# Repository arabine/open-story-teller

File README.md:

# Open Story Teller (OST)

|  Job | Status  |
|---|---|
| Story Editor  |   |

Open Story Teller is an Open Source project to provide guidelines and software to build your own story teller box (electronics, mechanical).

The main goal is to *not* make electronics boards but instead buy or reuse existing ones. This will allow you to easily repair your device with spare parts.

We propose a set of parts and firmware that is working well together but your are free to custom everything to fit your needs.

This project can be used as a base platform for any device that is composed by:
- A display (TFT...)
- An Audio output
- A SD card or memory
- Some Buttons / rotary encoder / potentiometer

<hr >

# Links

- http://openstoryteller.org/: main documentation, project news, guidelines, hardware shoping list...
- http://github.com/arabine/open-story-teller: source code, tickets, help

# Hardware parts

We propose the concept of bundles: a set of electronic boards that you can purchase quite easily (eg: Arduino, SeedStudio, Pimoroni, Adafruit, SparkFun...). The bundles are built around a central main board, the CPU, which comes with more or less peripherals (SD-Card reader, Wifi...).

Several bundles will be officially supported ; this is needed for us to ensure the portability of the firmware hardware interface layer.

Current bundles:
- Raspberry Pico (official DevKit) (ARM Cortex M0+)
- RISC-V based board (GD32VF103)

We plan to propose a mechanical enclosure ready to be printed for an official bundle.

See the documentation!

# Generic player architecture

The base software is highly portable and includes a micro virtual machine that executes the story scenario. This allow potential complex stories with loops, branches, user choices, randomization...

This project propose an minimal cross-platform GUI player application that can be used as a base project and VM implementation reference.

# StoryTeller Editor

We propose a basic editor tool to create your own stories. The generated story script runs on our micro virtual machine and allow generate complex stories.

Work in progress:
- Project management
- Story pack generation
- Basic nodes (media nodes, start and stop)

Planned nodes:
- Random
- Loop
- Conditional

# Story Player

The Story plater is a purely software implementation of a simple story player. It is provided as an example and a test device for the micro virtual machine. It is very portable and should run on a large number of platforms.

There are multiple implementations in this directory (Flutter, SDL, Raylib). The one that will be maintain is probably the Raylib version besause this framework is the easiest one to port on multiple platforms.

# Developer corner

## Build the Story Player

### Web version

Emscripten must be installed.

```
mkdir build-web && cd build-web
emcmake cmake .. -DPLATFORM=Web -DCMAKE_BUILD_TYPE=Debug
emmake make
```

# License

MIT License

Copyright (c) 2023 Anthony Rabine

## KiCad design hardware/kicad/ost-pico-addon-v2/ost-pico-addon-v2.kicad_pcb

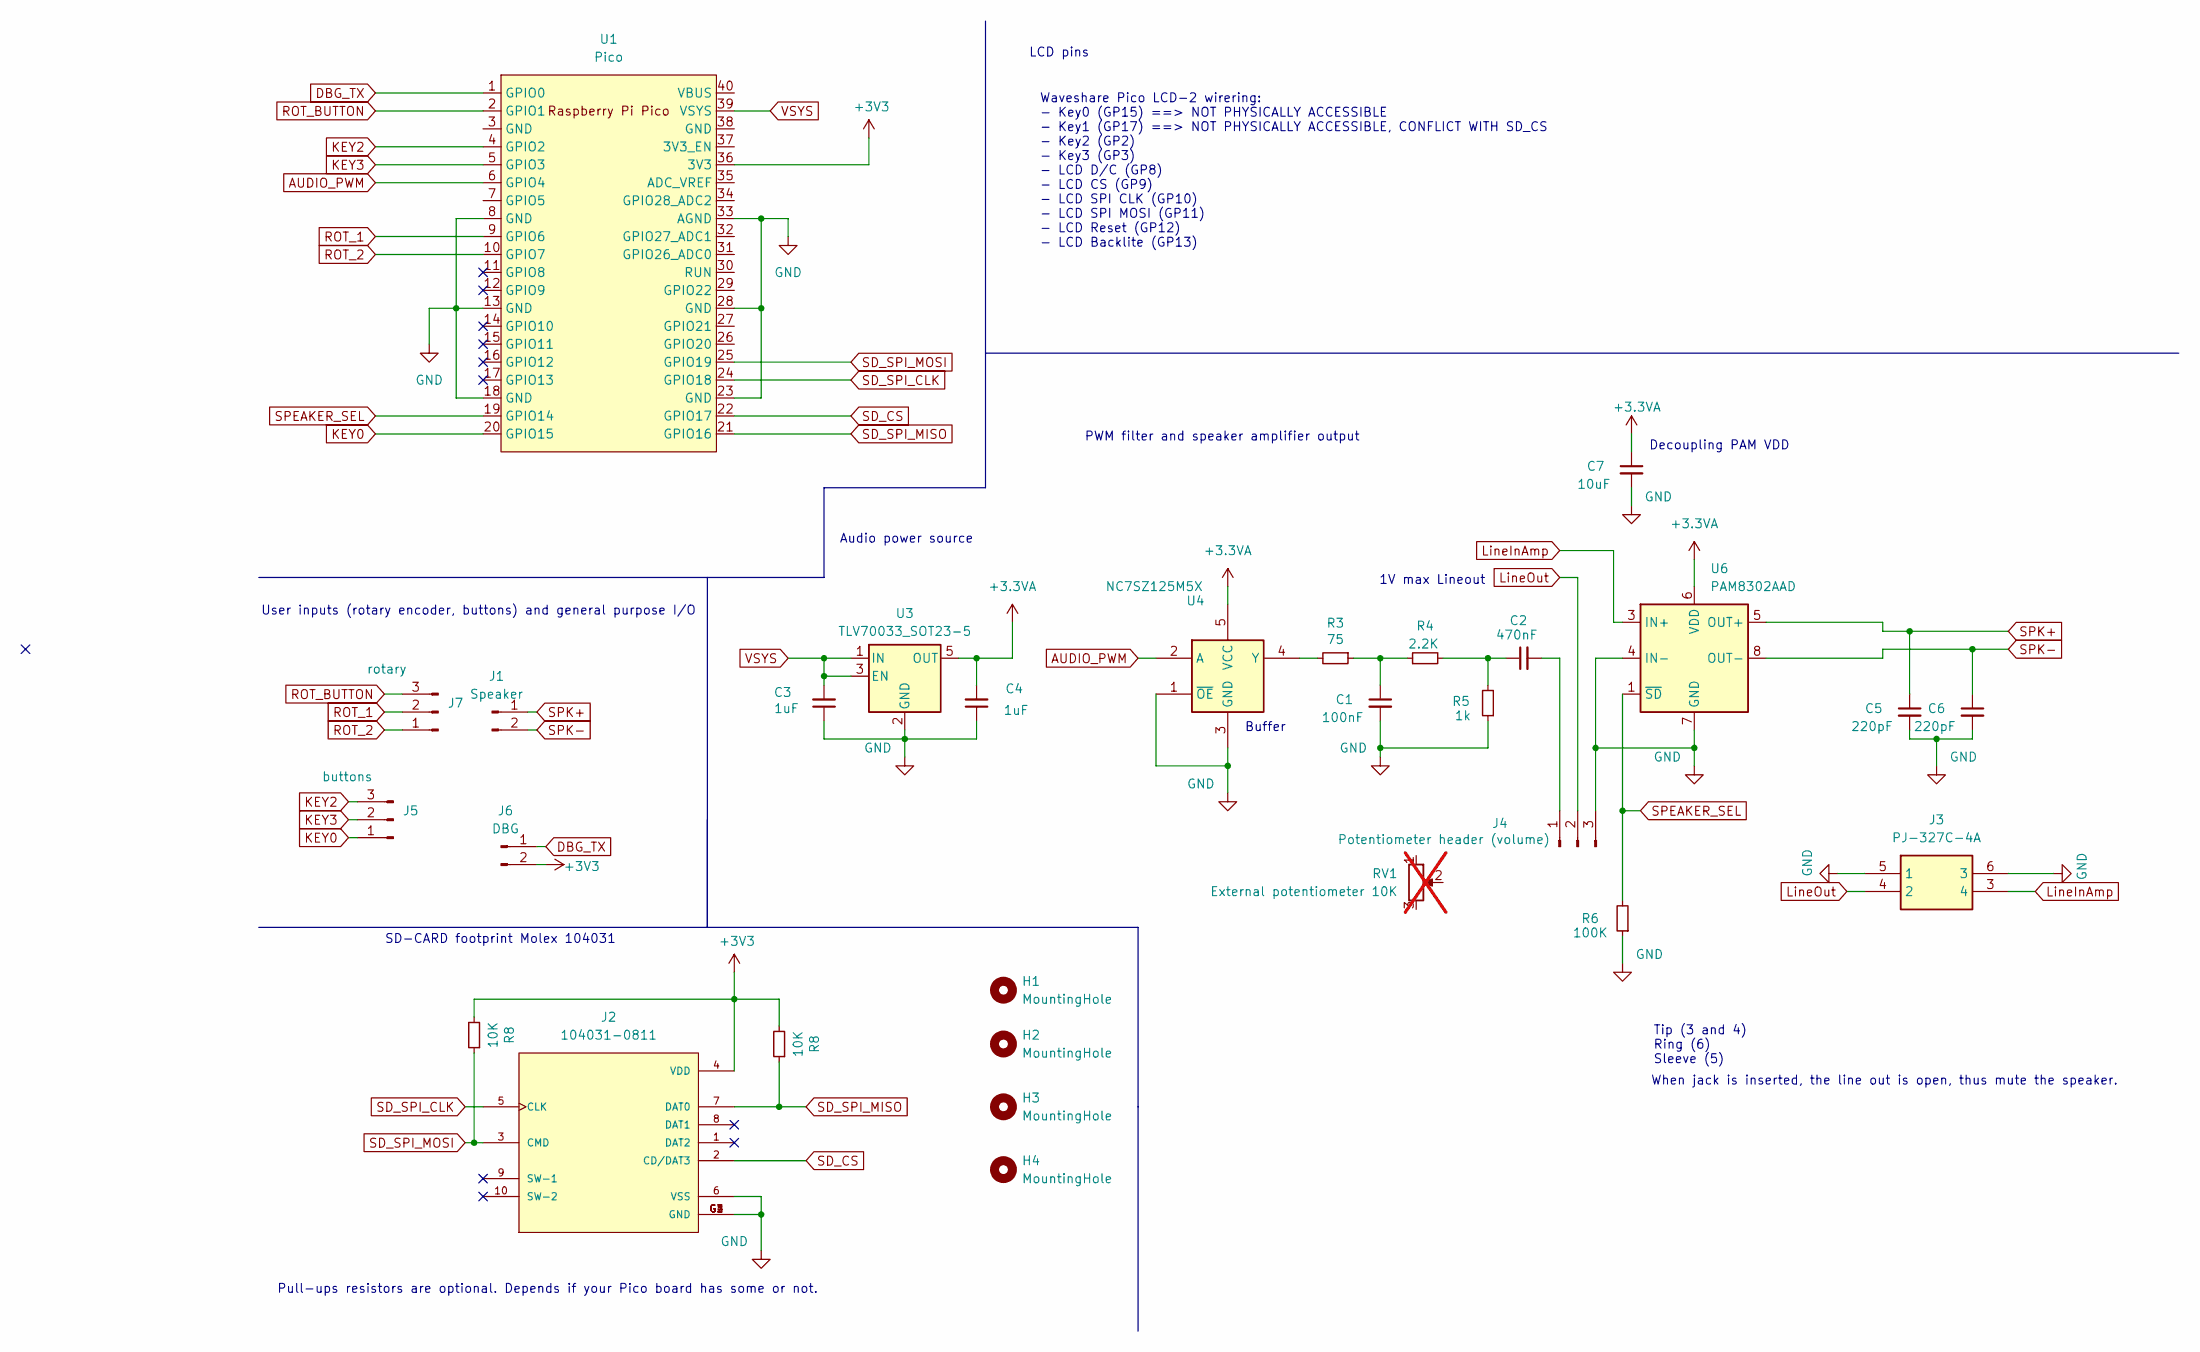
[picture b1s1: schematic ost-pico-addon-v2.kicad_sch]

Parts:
C1: 100nF; C_0805_2012Metric
C2: 470nF; C_0805_2012Metric
C3, C4: 1uF; C_0805_2012Metric
C5, C6: 220pF; C_0805_2012Metric
C7: 10uF; C_0805_2012Metric
H1, H2, H3, H4: MountingHole; MountingHole_2.5mm
J1: Speaker; PinHeader_1x02_P2.54mm_Vertical
J2: 104031-0811; MOLEX_104031-0811; PARTREV B2
J3: PJ-327C-4A; PJ327C4A; Manufacturer_Part_Number PJ-327C-4A
J4: Potentiometer header (volume); PinHeader_1x03_P2.54mm_Vertical
J5: buttons; PinHeader_1x03_P2.54mm_Vertical
J6: DBG; PinHeader_1x02_P2.54mm_Vertical
J7: rotary; PinHeader_1x03_P2.54mm_Vertical
R3: 75; R_0805_2012Metric
R4: 2.2K; R_0805_2012Metric
R5: 1k; R_0805_2012Metric
R6: 100K; R_0805_2012Metric
R8: 10K; R_0805_2012Metric
RV1: External potentiometer 10K; not fitted
U1: Pico; RPi_Pico_AddOn
U3: TLV70033_SOT23-5; SOT-23-5
U4: NC7SZ125M5X; SOT-23-5
U6: PAM8302AAD; MSOP-8_3x3mm_P0.65mm

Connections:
+3.3VA: C4.2, C7.1, U3.5 (OUT), U4.5 (VCC), U6.6 (VDD)
+3V3: J2.4 (VDD), J6.2, U1.36 (3V3); also elsewhere on the board
AUDIO_PWM: U1.6 (GPIO4), U4.2 (A)
DBG_TX: J6.1, U1.1 (GPIO0)
GND: C1.2, C3.1, C4.1, C5.2, C6.2, C7.2, J2.6 (VSS), J2.G1 (GND), J2.G2 (GND), J2.G3 (GND), J2.G4 (GND), J3.5 (1), J3.6 (3), J4.3, R5.1, R6.1, U1.8 (GND), U1.13 (GND), U1.18 (GND), U1.23 (GND), U1.28 (GND), U1.33 (AGND), U3.2 (GND), U4.1 (~OE), U4.3 (GND), U6.4 (IN-), U6.7 (GND)
KEY0: J5.1, U1.20 (GPIO15)
KEY2: J5.3, U1.4 (GPIO2)
KEY3: J5.2, U1.5 (GPIO3)
LineInAmp: J3.3 (4), U6.3 (IN+)
LineOut: J3.4 (2), J4.2
unnamed: C1.1, R3.1, R4.1
unnamed: C2.1, R4.2, R5.2
unnamed: C2.2, J4.1
unnamed: R3.2, U4.4 (Y)
ROT_1: J7.2, U1.9 (GPIO6)
ROT_2: J7.1, U1.10 (GPIO7)
ROT_BUTTON: J7.3, U1.2 (GPIO1)
SD_CS: J2.2 (CD/DAT3), U1.22 (GPIO17)
SD_SPI_CLK: J2.5 (CLK), U1.24 (GPIO18)
SD_SPI_MISO: J2.7 (DAT0), U1.21 (GPIO16); also elsewhere on the board
SD_SPI_MOSI: J2.3 (CMD), U1.25 (GPIO19); also elsewhere on the board
SPEAKER_SEL: R6.2, U1.19 (GPIO14), U6.1 (~SD)
SPK+: C5.1, J1.1, U6.5 (OUT+)
SPK-: C6.1, J1.2, U6.8 (OUT-)
VSYS: C3.2, U1.39 (VSYS), U3.1 (IN), U3.3 (EN)

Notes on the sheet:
PWM filter and speaker amplifier output
SD-CARD footprint Molex 104031
Buffer
Tip (3 and 4) Ring (6) Sleeve (5)
Decoupling PAM VDD
When jack is inserted, the line out is open, thus mute the speaker.
Waveshare Pico LCD-2 wirering: - Key0 (GP15) ==> NOT PHYSICALLY ACCESSIBLE - Key1 (GP17) ==> NOT PHYSICALLY ACCESSIBLE, CONFLICT WITH SD_CS - Key2 (GP2) - Key3 (GP3) - LCD D/C (GP8) - LCD CS (GP9) - LCD SPI CLK (GP10) - LCD SPI MOSI (GP11) - LCD Reset (GP12) - LCD Backlite (GP13)
User inputs (rotary encoder, buttons) and general purpose I/O
Pull-ups resistors are optional. Depends if your Pico board has some or not.
Audio power source
LCD pins
1V max Lineout

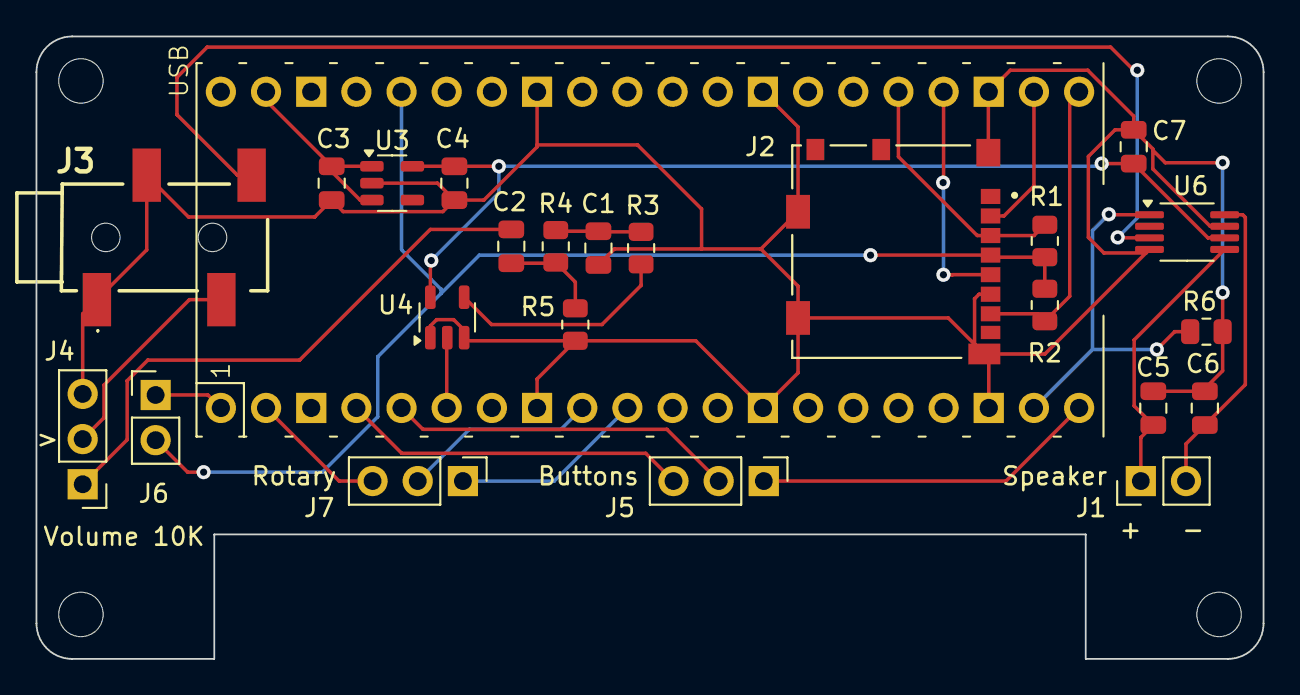
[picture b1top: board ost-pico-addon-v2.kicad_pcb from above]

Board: 2 copper layers, 69.0 x 35.0 mm, 28 parts (0 on the bottom side), 25 nets.

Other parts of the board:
R1, R2: 10K; R_0805_2012Metric

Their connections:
+3V3: R1.2, R2.2; also elsewhere on the board
SD_SPI_MISO: R2.1; also elsewhere on the board
SD_SPI_MOSI: R1.1; also elsewhere on the board

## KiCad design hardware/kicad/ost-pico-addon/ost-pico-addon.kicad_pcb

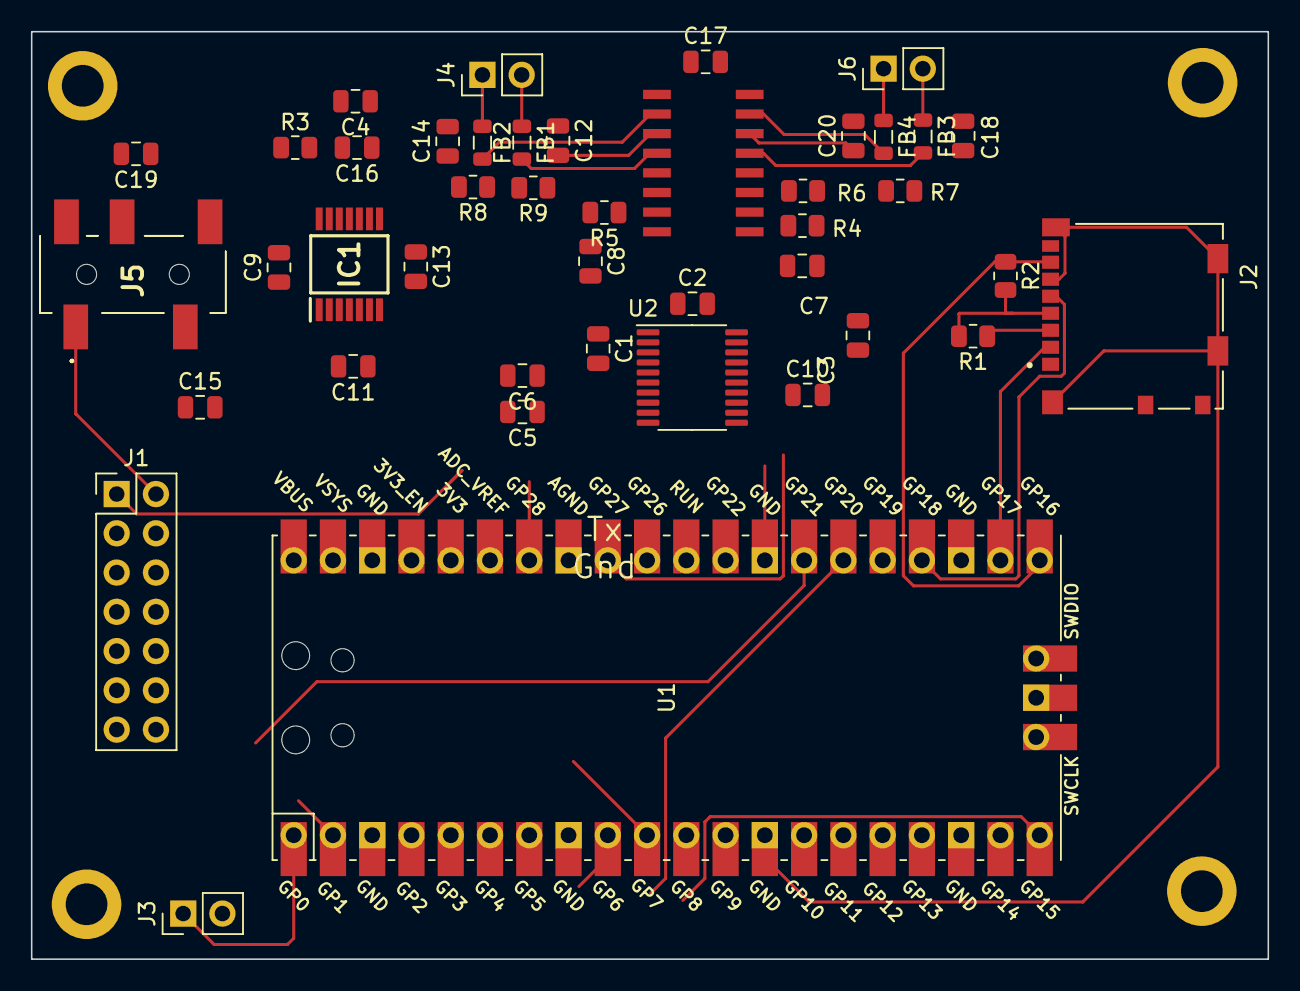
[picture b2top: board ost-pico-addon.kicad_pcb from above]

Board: 2 copper layers, 80.0 x 60.0 mm, 47 parts (0 on the bottom side), 54 nets.

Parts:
C1, C2, C5, C6: 2.2uF; C_0805_2012Metric
C3: 100nF; C_0805_2012Metric
C4, C7, C8, C9, C10, C11: 1uF; C_0805_2012Metric
C12, C14, C18, C20: 270pF; C_0805_2012Metric
C13, C16: 47uF/6.3V/20%/X5R/C0805; C_0805_2012Metric
C15, C19: 47uF; C_0805_2012Metric
C17: 100nF/50V/20%/Y5V/C0603; C_0805_2012Metric
FB1, FB2, FB3, FB4: FB0805; L_0805_2012Metric
H1, H2, H3, H4: MountingHole; MountingHole_2.7mm_M2.5_ISO14580_Pad
IC1: TPA6139A2PWR; SOP65P640X120-14N
J1: buttons; PinHeader_2x07_P2.54mm_Vertical
J2: 104031-0811; MOLEX_104031-0811
J3: DBG_TX; PinHeader_1x02_P2.54mm_Vertical
J4: SPK_LEFT; PinHeader_1x02_P2.54mm_Vertical
J5: PJ-327U-SMT; PJ327USMT
J6: SPK_RIGHT; PinHeader_1x02_P2.54mm_Vertical
R1, R2: 10K; R_0805_2012Metric
R3: 49K; R_0805_2012Metric
R4, R5: 10k; R_0805_2012Metric
R6: 1K; R_0805_2012Metric
R7: 1K(n.a.); R_0805_2012Metric
R8: 100K; R_0805_2012Metric
R9: 0K; R_0805_2012Metric
U1: Pico; RPi_Pico_SMD_TH
U2: PCM5102A; TSSOP-20_4.4x6.5mm_P0.65mm
U3: PAM8003; SO16

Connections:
+3V3: C4.1, C13.1, C16.1, C17.2, IC1.10 (VDD), J1.1, J2.4 (VDD), R1.2, R2.2, R6.2, R8.2, U1.36 (3V3), U2.1 (CPVDD), U2.8 (AVDD), U2.17 (XSMT), U2.20 (DVDD), U3.1 (PVDDL), U3.9 (VDD), U3.16 (PVDDR)
DBG_TX: J3.1, U1.1 (GPIO0)
GND: C2.2, C3.1, C4.2, C10.2, C11.2, C12.2, C13.2, C14.1, C16.2, C17.1, C18.2, C20.1, IC1.3 (GND_1), IC1.11 (GND_2), J1.2, J2.6 (VSS), J2.G1 (GND), J2.G2 (GND), J2.G3 (GND), J2.G4 (GND), J3.2, J5.2, R3.2, R7.1, U1.3 (GND), U1.8 (GND), U1.13 (GND), U1.18 (GND), U1.23 (GND), U1.28 (GND), U1.33 (AGND), U1.38 (GND), U2.3 (CPGND), U2.9 (AGND), U2.10 (DEMP), U2.11 (FLT), U2.12 (SCK), U2.16 (FMT), U2.19 (DGND), U3.3 (PGNDL), U3.8 (GND), U3.14 (PGNDR)
HP_DET: IC1.4 (~MUTE), J5.6, R8.1, R9.2
HP_OUTL: C15.2, IC1.2 (OUT_L)
HP_OUTR: C19.1, IC1.13 (OUT_R)
I2S_DATA: U1.34 (GPIO28_ADC2), U2.14 (DIN)
I2S_LRCK: U1.32 (GPIO27_ADC1), U2.15 (LRCK)
I2S_SCLK: U1.31 (GPIO26_ADC0), U2.13 (BCK)
IO_1: J1.13, U1.29 (GPIO22)
IO_2: J1.11, U1.27 (GPIO21)
IO_3: J1.9, U1.26 (GPIO20)
IO_4: J1.7, U1.6 (GPIO4)
IO_5: J1.5, U1.7 (GPIO5)
IO_6: J1.3, U1.19 (GPIO14)
KEY0: J1.8, U1.20 (GPIO15)
KEY2: J1.6, U1.4 (GPIO2)
KEY3: J1.4, U1.5 (GPIO3)
LINE_OUT_L: C6.1, C8.2, U2.6 (OUTL)
LINE_OUT_R: C5.1, C7.2, U2.7 (OUTR)
unnamed: C7.1, R4.2
unnamed: C8.1, R5.2
unnamed: C15.1, J5.3
unnamed: C19.2, J5.5
unnamed: C6.2, IC1.1 (-IN_L)
unnamed: C5.2, IC1.14 (-IN_R)
unnamed: C9.1, IC1.6 (CN)
unnamed: C9.2, IC1.9 (CP)
unnamed: IC1.12 (GAIN), R3.1
unnamed: C11.1, IC1.5 (VSS)
unnamed: C14.2, FB2.1, J4.1
unnamed: C12.1, FB1.1, J4.2
unnamed: C20.2, FB4.1, J6.1
unnamed: C18.1, FB3.1, J6.2
unnamed: C1.2, U2.4 (CAPM)
unnamed: C1.1, U2.2 (CAPP)
unnamed: C3.2, U2.18 (LDOO)
unnamed: C2.1, U2.5 (VNEG)
unnamed: R9.1, U3.5 (#SHDN)
unnamed: R5.1, U3.7 (INL)
unnamed: R4.1, U3.10 (INR)
unnamed: FB2.2, U3.2 (OUTLN)
unnamed: FB1.2, U3.4 (OUTLP)
unnamed: FB4.2, U3.15 (OUTRN)
unnamed: FB3.2, U3.13 (OUTRP)
unnamed: R6.1, R7.2, U3.12 (VOL)
unnamed: C10.1, U3.6 (VREF)
ROT_1: J1.10, U1.9 (GPIO6)
ROT_2: J1.12, U1.10 (GPIO7)
ROT_BUTTON: J1.14, U1.2 (GPIO1)
SD_CS: J2.2 (CD/DAT3), U1.22 (GPIO17)
SD_SPI_CLK: J2.5 (CLK), U1.24 (GPIO18)
SD_SPI_MISO: J2.7 (DAT0), R2.1, U1.21 (GPIO16)
SD_SPI_MOSI: J2.3 (CMD), R1.1, U1.25 (GPIO19)

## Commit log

2023-04-18 add files (swicth to mono-repo)
2023-04-21 repair build for editor, add website skeletton
2023-04-22 testing vitepress
2023-04-22 Update vitepress.yml
    specify docs subdir
2023-04-23 Vitepress: try language, add image chooser for media node
2023-04-25 Add log window and QDebug redirections
2023-04-25 fix skip and call in VM, add temporary registers
2023-04-26 New parser for lines + constants (allow labels in constants)
2023-04-27 Working media loop + fix call VM
2023-04-28 project management load/save/new (WIP)
2023-05-02 Update docs
2023-05-02 docs: fix build
2023-05-07 New project dialog
2023-05-11 Open/load project
2023-05-11 First version of OST RPI Pico mother board on kicad
2023-05-12 story run icon, save/load resources
2023-05-14 switched to nlohmann Json
2023-05-15 (WIP) Code generation
2023-05-17 save docks visibility, fix node, media node complete, vpfr generation (WIP)
2023-05-22 Build and run a node in VM, first!
2023-05-22 fix load out nodes count
2023-05-23 Replaced Qt audio by miniaudio
2023-05-24 media loop ok, add jumpr assembly, remove old arts
2023-05-25 Working pack! fix VM, new icons...
2023-05-28 static build of nodeeditor
2023-05-28 fix windows build
2023-05-28 Add innosetup
2023-05-29 Auto stash before merge of "main" and "origin/main"
2023-05-30 Update doc + story player (wip) + packaging (wip)
2023-05-30 fix logo for docs (tentative)
2023-05-31 First working version of the software player
2023-05-31 Update docs and readme with story player
2023-05-31 More docs, fix CMake build, add VSCode config files
2023-06-01 fix doc
2023-06-05 New SDCARD layer platform agnostic
2023-06-07 update pico docs
2023-06-18 Add audio file tool
2023-07-12 basic os (WIP)
2023-07-13 Add mailbox and two tasks switching example
2023-07-16 Working mailbox implementation
2023-07-18 tickless algorithm working!
2023-07-21 stable QoRTOS (for now), before cleaning
2023-07-21 External stack for QoRTOS
2023-07-24 new: sdcard agnostic middleware layer + audio read benchmark
2023-07-25 fix qor mailboxes + all is in place for audio with thread, dma and irq
2023-07-26 Working sound! Yeahhh
2023-07-26 Add VM task and source files to build system, wip: qor API
2023-07-27 New: HMI thread (user inputs and LCD manager)
2023-07-28 Switched to QOI file format
2023-07-29 firmware: put tasks into dedicated files with clean API, prepare story title image and sounds
2023-07-31 fix sdcard buffer overflow, fix switch case, use of TLV index file for stories
2023-07-31 Parse index file (TLV) for multiple stories
2023-08-02 fix: mailbox buffer type, load story, button events (WIP)
2023-08-05 Add USB mass storage device (WIP) + rework task state machines
2023-08-07 QOR PendSV priority fix,
2023-08-08 changed hmi task into usb_task, qor fix, buttons and rotary encoder driver
2023-08-09 several vc++ compiler fixes
2023-08-09 editor: add about box, add mp3 converter, one asset for all media
2023-08-10 (wip) mono and dynamic sample rate support
2023-08-10 VisualC++ fixes
2023-08-10 Add static before inline
2023-08-10 add dl to link libraries
2023-08-10 git workflow for Appimage generation
2023-08-11 fix build missing logo
2023-08-11 (WIP) Action for windows build
2023-08-11 fixes actions for windows
2023-08-11 add windows setup
2023-08-12 first mono support (still glitches in audio)
2023-08-18 USB write success (still very slow, see errors in DMESG
2023-09-20 pinout and routing changes
2023-09-20 change button port pinout
2023-11-02 story editor v2
2023-11-02 fix build story editor v2
2023-11-07 editor v2 + usb host tests
2023-11-19 media node fixes + (WIP) open project
2023-12-10 Open and draw a story teller project format
2023-12-13 [EDITOR] new resource manager
2023-12-13 renamed directory
2023-12-16 New properties window (moved node parameters to this window)
2023-12-16 fix loading project
2023-12-17 save project (WIP), bugs in conection ids and missing image resources
2023-12-19 fix project saving, resource management and media node properties change
2023-12-21 Build binary, code display, errors management
2023-12-21 fix bad left/right line trim + fix wanings
2023-12-23 better event, better audio, add QOI to emulator, emulator is executed
2023-12-23 changed editor screenshot
2023-12-24 fix windows build, changed github actions to remove Qt steps
2023-12-25 fix windows build, remove console window
2023-12-25 test win build
2023-12-25 rm gh workflows to build editor
2023-12-26 Add Dockerfile + add cross build for WIn32 + Add create node
2023-12-27 Recent projects management + working Link creation
2023-12-27 Simpler way to create new project, project path in title bar
2023-12-30 Docs update and news section, ok button, versioing, about and project properties (wip)
2024-01-07 Fix firmware build, more docs
2024-01-07 More docs on the story formats
2024-01-15 (WIP) Library Manager
2024-01-16 Factorised more code in LabraryManager and StoryProject, used widely
2024-01-20 cpack update + github workflow (linux)
2024-01-20 gh actions test
2024-01-20 gh actions fix
2024-01-21 removed unecessary package
2024-01-21 chg build system
2024-01-21 fix dir
2024-01-22 Add MacOS bundle generation (WIP) + Macos build fixes
2024-01-22 mac dmg (wip)
2024-03-10 fix windows build, new build script for win32 setup executable generation
2024-03-10 fix linux build
2024-03-10 Add win32 build to CI
2024-03-10 fix ci
2024-03-10 fix ci2
2024-03-10 fix regression
2024-03-26 Pico audio with 3 audio chips (complex)
2024-03-26 (WIP library store manager)
2024-04-01 SDL 3 + curl thread download manager
2024-04-01 Use SDL3_Image + multiple bug fixes
2024-04-02 Download manager from sharepoint
2024-04-22 (wip) Studio format import, (wip) ogg decoder files, (ipgrade) imguifiledialog
2024-04-22 moved somes files, add vorbis playback support
2024-04-24 more separation between node UI logic and editor, working Studio format support
2024-04-24 Add OGG converter
2024-04-24 tentative: fix SDL link
2024-04-24 (wip) library story selection and export to device
2024-04-27 librarymanager: (wip) selection and copy to device
2024-04-30 Big overall architecture change: separation between display and story model
2024-05-02 add logger, fix mem leak, pack copy to device finished.
2024-05-06 fix TLV, add docs, editor: add title name and sound, new story player app in flutter
2024-05-14 Fix project loading duplicate nodes, formats moved
2024-05-14 switched audio from miniaudio to SDL_mixer
2024-05-15 Fix media output format, fix link creation
2024-05-17 editor: Fix node model initialization, add binary load
2024-05-17 first working app
2024-05-17 Files for version 1.0
2024-05-20 (wip) Flutter App v1.1: fix logo, fix build warning (updated to last), freezed SDL libraries to a tag
2024-05-20 (WIP) Code debug: add breakpoint button
2024-05-23 Add comparison chip32 instructions, add debugger, add CPU window
2024-05-28 Chip32 asm: supports hex and binary numbers, audio can be cancelled, add support to event masks
2024-05-28 story-player flutter: integrated new event mask + shared preferences
2024-05-28 (WIP) Story machine specific Chip32 management
2024-05-28 Add syscall 3, home button exit VM on choice media
2024-08-06 Add function node with sub editor
2024-08-30 Create separated core (WIP) GUI agnostic, new sub pages for functions
2024-12-28 new Kicad audio hat
2024-12-28 update imgui, home-made code viewer (not editor!)
2024-12-30 (WIP) Commercial import
2025-01-03 (WIP) new Download manager, download of commercial DB
2025-01-04 Usage of CPM package manager for CMake, add CivetWeb
2025-01-07 Raylib build for web + minimal front-end page, stand alone story-vm project
2025-01-07 editor: fix build
2025-01-09 First web server route, use of preact for raylib html version
2025-01-10 dedicated directory for story web version
2025-01-13 fetch stories list from libraryes ok
2025-01-13 Multiple fixes on project management, fix resource copy bugs
2025-01-14 Import commercial nearly complete
2025-01-17 many many fixes for commercial story import, wip on transitions
2025-01-19 working import commercial stories
2025-01-20 Fix win32 build, fix duplicate resource files, fix VM stop
2025-01-21 fix unit tests for chip32, better debugger
2025-01-28 usage of submodules instead of git fetch multiple fixes/file moves
2025-01-28 civetweb options
2025-02-01 fix mingw64 build, add docker image for linux build
2025-02-02 fix ci and nsis package generation
2025-02-02 fix deprecated version of gh action
2025-02-03 Add MBedTLS as a submodule
2025-02-03 Add mbed submodule to version 3.6.2
2025-02-16 fix CI (tentative)
2025-02-18 Fix CI (link and missing libfuse in base image
2025-03-08 Chip32: added two instructions and a macro pre-processor
2025-03-09 (wip) compiler with ast
2025-03-09 ast unit test
2025-04-06 Add main entry point, fix some bugs, continue AST compilation
2025-04-09 First version of AST/flow/assembly generation base classes, arch seems ok
2025-04-17 Good architecture between AST and assembly generation, still WIP
2025-04-22 Better custom AST builder using kahn algorithm
2025-04-22 First working assembly from nodes (cli), youpi
2025-04-22 make story editor build
2025-04-23 Build splitted to allow multi pages compilation, more widgets
2025-04-24 Multiple runtime fixes, first build+execution with graphical nodes
2025-04-25 Remove story in library + save/load variables
2025-04-26 Variables in context, fix variable and print node save data in JSON
2025-06-20 Created Node Factory in dedicated class to allow custom nodes not linked to one project
2025-06-23 fix Flutter build
2025-07-06 Start of module editor with pre version of independant factory
2025-07-16 Separated call function module, better module support with type
2025-07-27 Module save/load
2025-07-27 (WIP) Refactoring MainWindow, open existing module for edit (still buggy)
2025-07-28 Fix open exiting module
2025-08-07 Intermediatre commit: separation between logic and UI
2025-08-15 wip move out logic from ui
2025-08-24 Build and run ok
2025-08-26 Working variable edior for modules
2025-08-28 (wip) compilation of module
2025-09-02 Replace ImGuiNodeEditor by ImNodeFlow (build and execute ok, missing widget content)
2025-09-04 Add selection for property display
2025-09-07 Function entry/exit nodes + custom socket (wip)
2025-10-01 custom socket styling
2025-10-01 load/save module success, better toaster
2025-10-01 fix build of modules
2025-10-02 Add error list dock window, cleaned some nodes
2025-10-02 removed exit node, nex function widget
2025-10-02 missing files
2025-10-02 cleaning + label from node base
2025-10-02 Added localization API and helpers
2025-10-03 Working custom socket
2025-10-03 Compilation and load of module
2025-10-03 Add VM console output !
2025-10-04 merged tests all in core now, added print test
2025-10-05 fix win32 build (tentative)
2025-10-06 Add TAC in compile pipeline
2025-10-06 Fixed data connection, compilation order and print format
2025-10-07 Add DATA and BSS RAM sections, crate binary format with header
2025-10-12 (WIP) new binary format
2025-10-15 Big update on machine class, fix addressing lcons, load etc.
2025-10-16 Using same objets between labels and instructions + fix load and store
2025-10-16 Make editor full use of Machine class
2025-10-16 fix ram view
2025-10-17 viariables not clear before project load
2025-10-17 Add branch node, unit test and fixes
2025-10-18 (wip) Instructions unit test (complete)
2025-10-18 merged jump/call implementation, removed jumpr
2025-10-19 Add all system calls as dedicated nodes
2025-10-20 Modified TAC for all new syscall widgets
2025-10-20 Add loops nodes !
2025-10-21 Add module properties popup.
2025-10-24 new function entry/exit nodes with parameters
